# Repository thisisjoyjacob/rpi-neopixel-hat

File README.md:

# rpi-neopixel-hat

Raspberry pi 3B+ Neopixel hat

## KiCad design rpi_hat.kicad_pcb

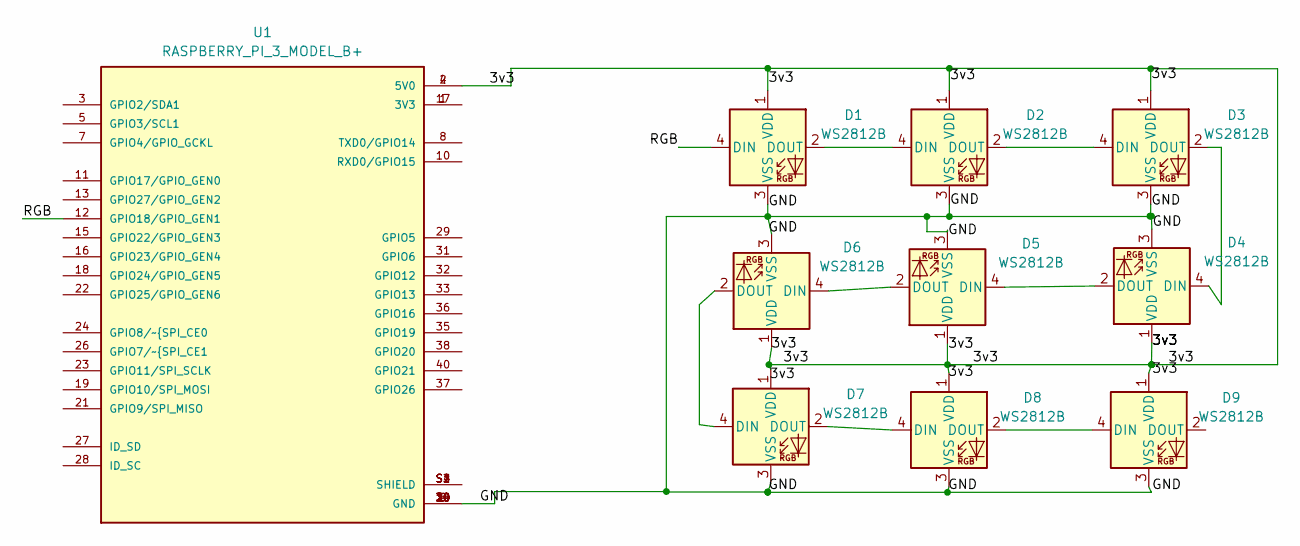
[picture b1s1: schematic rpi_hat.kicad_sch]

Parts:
D1, D2, D3, D4, D5, D6, D7, D8, D9: WS2812B; LED_WS2812B_PLCC4_5.0x5.0mm_P3.2mm
U1: RASPBERRY_PI_3_MODEL_B+; MODULE_RASPBERRY_PI_3_MODEL_B+; PARTREV 1.0

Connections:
/3v3: D1.1 (VDD), D2.1 (VDD), D3.1 (VDD), D4.1 (VDD), D5.1 (VDD), D6.1 (VDD), D7.1 (VDD), D8.1 (VDD), D9.1 (VDD), U1.2 (5V0), U1.4 (5V0)
/GND: D1.3 (VSS), D2.3 (VSS), D3.3 (VSS), D4.3 (VSS), D5.3 (VSS), D6.3 (VSS), D7.3 (VSS), D8.3 (VSS), D9.3 (VSS), U1.6 (GND), U1.9 (GND), U1.14 (GND), U1.20 (GND), U1.25 (GND), U1.30 (GND), U1.34 (GND), U1.39 (GND)
/RGB: D1.4 (DIN), U1.12 (GPIO18/GPIO_GEN1)
unnamed: D1.2 (DOUT), D2.4 (DIN)
unnamed: D2.2 (DOUT), D3.4 (DIN)
unnamed: D3.2 (DOUT), D4.4 (DIN)
unnamed: D4.2 (DOUT), D5.4 (DIN)
unnamed: D5.2 (DOUT), D6.4 (DIN)
unnamed: D6.2 (DOUT), D7.4 (DIN)
unnamed: D7.2 (DOUT), D8.4 (DIN)
unnamed: D8.2 (DOUT), D9.4 (DIN)
unnamed: U1.1 (3V3), U1.17 (3V3)
unnamed: U1.S1 (SHIELD), U1.S2 (SHIELD), U1.S3 (SHIELD), U1.S4 (SHIELD)

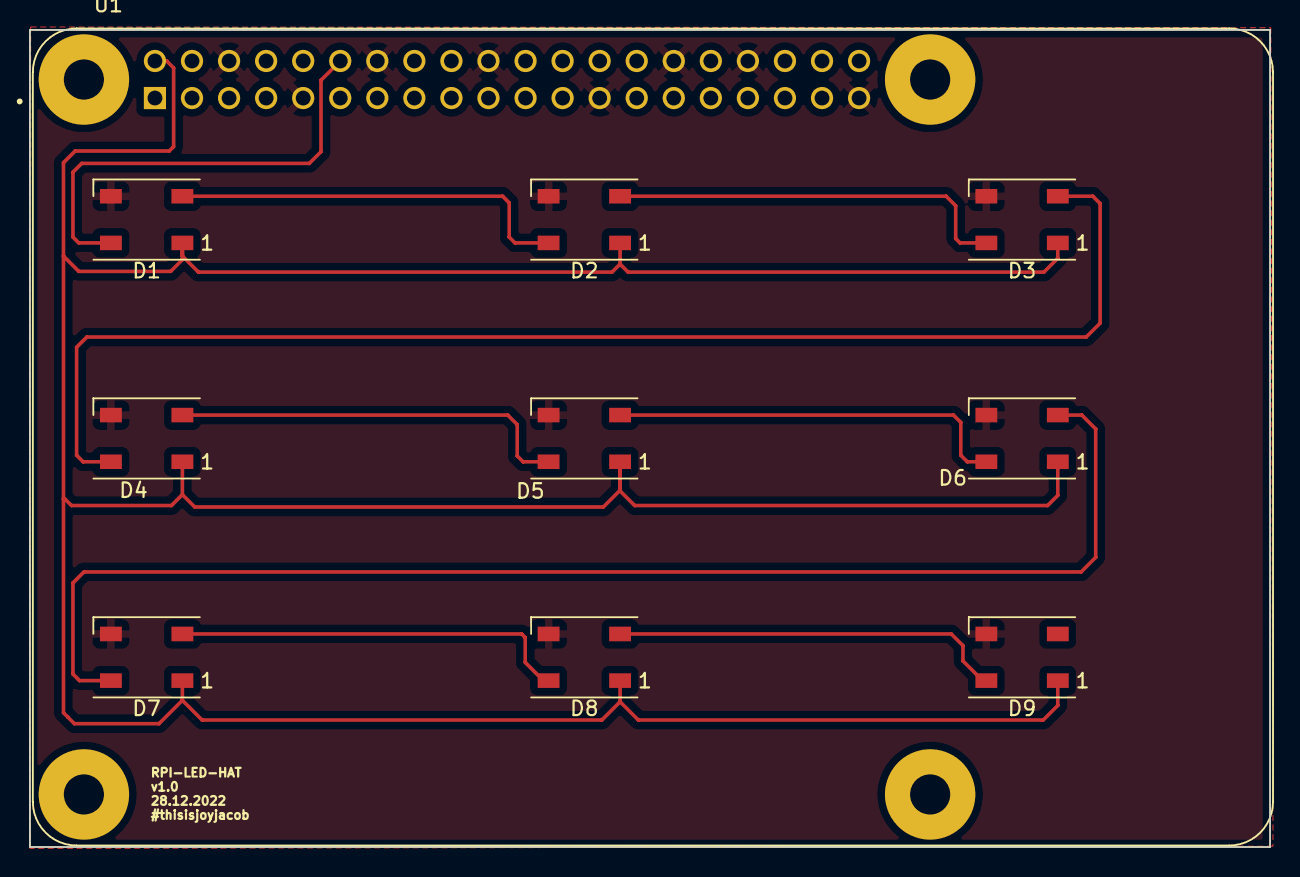
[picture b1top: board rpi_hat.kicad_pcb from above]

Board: 2 copper layers, 85.0 x 56.0 mm, 10 parts (0 on the bottom side), 13 nets.

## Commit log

2022-12-28 rpi neopixel hat v1.0 commit
2022-12-28 pic added
2022-12-28 hat changes in design and ideation
